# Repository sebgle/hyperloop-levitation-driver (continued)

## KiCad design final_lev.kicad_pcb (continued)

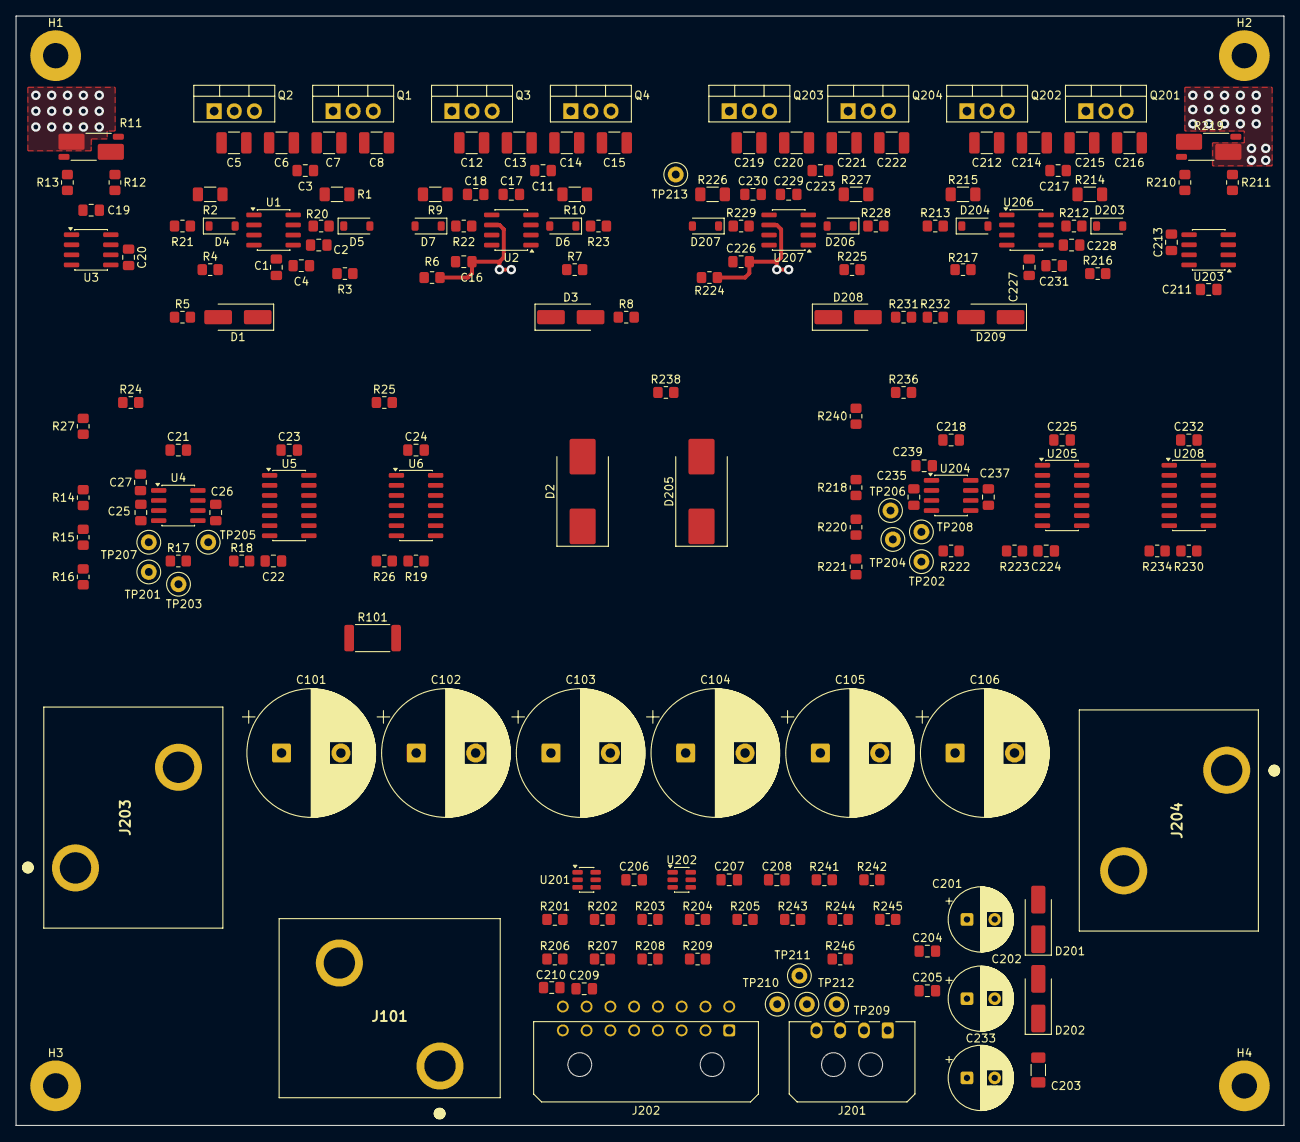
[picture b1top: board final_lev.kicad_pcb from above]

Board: 4 copper layers, 160.0 x 140.0 mm, 197 parts (0 on the bottom side), 93 nets.

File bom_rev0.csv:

"Reference","Qty","Value","DNP","Exclude from BOM","Exclude from Board","Exclude from Simulation","Exclude from Position Files","Footprint","Datasheet","Voltage"
"C1,C4,C16,C18,C226,C227,C230,C231","8","1uF","","","","","${EXCLUDE_FROM_POS_FILES}","Capacitor_SMD:C_0805_2012Metric_Pad1.18x1.45mm_HandSolder","","25V"
"C2,C3,C11,C17,C20,C21,C22,C23,C204,C205,C206,C207,C208,C209,C210,C213,C217,C218,C223,C224,C225,C228,C229","23","100nF","","","","","${EXCLUDE_FROM_POS_FILES}","Capacitor_SMD:C_0805_2012Metric_Pad1.18x1.45mm_HandSolder","","100V,25V"
"C5,C6,C7,C8,C12,C13,C14,C15,C212,C214,C215,C216,C219,C220,C221,C222","16","1uF","","","","","${EXCLUDE_FROM_POS_FILES}","Capacitor_SMD:C_1210_3225Metric_Pad1.33x2.70mm_HandSolder","","100V"
"C19,C211","2","1nF","","","","","${EXCLUDE_FROM_POS_FILES}","Capacitor_SMD:C_0805_2012Metric_Pad1.18x1.45mm_HandSolder","","50V"
"C101,C102,C103,C104,C105,C106","6","470uF","","","","","${EXCLUDE_FROM_POS_FILES}","Capacitor_THT:CP_Radial_D18.0mm_P7.50mm","","100V"
"C201,C202","2","220uF","","","","","${EXCLUDE_FROM_POS_FILES}","Capacitor_THT:CP_Radial_D8.0mm_P3.50mm","","25V"
"C203","1","10uF","","","","","${EXCLUDE_FROM_POS_FILES}","Capacitor_SMD:C_1206_3216Metric_Pad1.33x1.80mm_HandSolder","","25V"
"D1,D3,D208,D209","4","ES1D","","","","","${EXCLUDE_FROM_POS_FILES}","Diode_SMD:D_SMA_Handsoldering","",""
"D2,D205","2","5.0SMDJ70A","","","","","${EXCLUDE_FROM_POS_FILES}","Diode_SMD:D_SMC_Handsoldering","",""
"D4,D5,D6,D7,D203,D204,D206,D207","8","1N4148W","","","","","${EXCLUDE_FROM_POS_FILES}","Diode_SMD:D_SOD-123","",""
"D201,D202","2","SS34","","","","","${EXCLUDE_FROM_POS_FILES}","Diode_SMD:D_SMA_Handsoldering","",""
"F101","1","70A","","","","","${EXCLUDE_FROM_POS_FILES}","","",""
"J101","1","+60V IN","","","","","${EXCLUDE_FROM_POS_FILES}","","",""
"J201","1","RAILS IN","","","","","${EXCLUDE_FROM_POS_FILES}","","",""
"J202","1","CONTROL","","","","","${EXCLUDE_FROM_POS_FILES}","","",""
"J203","1","YOKE 1","","","","","${EXCLUDE_FROM_POS_FILES}","","",""
"J204","1","YOKE 2","","","","","${EXCLUDE_FROM_POS_FILES}","","",""
"Q1,Q2,Q3,Q4,Q201,Q202,Q203,Q204","8","IRF100B201","","","","","${EXCLUDE_FROM_POS_FILES}","Package_TO_SOT_THT:TO-220-3_Vertical","https://www.infineon.com/assets/row/public/documents/24/49/i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",""
"R1,R2,R9,R10,R214,R215,R226,R227","8","10R","","","","","${EXCLUDE_FROM_POS_FILES}","Resistor_SMD:R_1206_3216Metric_Pad1.30x1.75mm_HandSolder","",""
"R3,R4,R6,R7,R14,R16,R17,R18,R19,R201,R202,R203,R204,R216,R217,R218,R221,R222,R223,R224,R225,R230","22","10k","","","","","${EXCLUDE_FROM_POS_FILES}","Resistor_SMD:R_0805_2012Metric_Pad1.20x1.40mm_HandSolder","",""
"R5,R8,R231,R232","4","1R","","","","","${EXCLUDE_FROM_POS_FILES}","Resistor_SMD:R_0805_2012Metric_Pad1.20x1.40mm_HandSolder","",""
"R11,R219","2","1m","","","","","${EXCLUDE_FROM_POS_FILES}","Resistor_SMD:R_Shunt_Vishay_WSK2512_6332Metric_T2.66mm","",""
"R12,R13,R210,R211","4","10R","","","","","${EXCLUDE_FROM_POS_FILES}","Resistor_SMD:R_0805_2012Metric_Pad1.20x1.40mm_HandSolder","",""
"R15,R220","2","24k","","","","","${EXCLUDE_FROM_POS_FILES}","Resistor_SMD:R_0805_2012Metric_Pad1.20x1.40mm_HandSolder","",""
"R20,R21,R22,R23,R212,R213,R228,R229","8","4.7R","","","","","${EXCLUDE_FROM_POS_FILES}","Resistor_SMD:R_0805_2012Metric_Pad1.20x1.40mm_HandSolder","",""
"R101","1","22k","","","","","${EXCLUDE_FROM_POS_FILES}","Resistor_SMD:R_1206_3216Metric_Pad1.30x1.75mm_HandSolder","",""
"R205,R206,R207,R208,R209","5","100R","","","","","${EXCLUDE_FROM_POS_FILES}","Resistor_SMD:R_0805_2012Metric_Pad1.20x1.40mm_HandSolder","",""
"U1,U2,U206,U207","4","IR2184","","","","","${EXCLUDE_FROM_POS_FILES}","Package_SO:SOIC-8_3.9x4.9mm_P1.27mm","https://www.infineon.com/assets/row/public/documents/24/49/i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",""
"U3,U203","2","INA240A1D","","","","","${EXCLUDE_FROM_POS_FILES}","Package_SO:SOIC-8_3.9x4.9mm_P1.27mm","http://www.ti.com/lit/ds/symlink/ina240.pdf",""
"U4,U204","2","LM393","","","","","${EXCLUDE_FROM_POS_FILES}","Package_SO:SOIC-8_3.9x4.9mm_P1.27mm","http://www.ti.com/lit/ds/symlink/lm393.pdf",""
"U5,U205","2","74HC74","","","","","${EXCLUDE_FROM_POS_FILES}","Package_SO:SOIC-14_3.9x8.7mm_P1.27mm","https://assets.nexperia.com/documents/data-sheet/74HC_HCT74.pdf",""
"U201,U202","2","74LVC2G17","","","","","${EXCLUDE_FROM_POS_FILES}","Package_TO_SOT_SMD:SOT-23-6","http://www.ti.com/lit/sg/scyt129e/scyt129e.pdf",""
